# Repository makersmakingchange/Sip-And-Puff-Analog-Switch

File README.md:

# Sip and Puff Switch

The Sip and Puff Switch is an assistive technology that enables a user to control a device by using their mouth to "sip"(inhale) or "puff"(exhale) on a straw, tube or ‘wand’. It is primarily used by people with limited or no limb movement. The Sip and Puff Switch can be connected directly to an assistive device with a 3.5 mm jack or to a computer or smartphone using a suitable switch interface.

The Sip and Puff Switch has two 3.5 mm mono outputs so it can control two devices. The sip threshold and puff threshold are adjustable. The switch is powered by two CR2032 lithium coin cell batteries.

## More info at

- [Makers Making Change Project Page](https://www.makersmakingchange.com/project/sip-and-puff-switch/)

## Getting Started

### 1. Order the Off-The-Shelf Components
The [Bill of Materials](/Documentation/SPA_BOM_v1.0.xlsx) lists all of the parts and components required to build the Sip and Puff switch.

### 2. Order the Custom Printed Circuit Board (PCB)
The Sip and Puff Switch uses a custom PCB to mount all of the electronic components. Refer to [MMC_PCB_Fabrication_Manual](/Documentation/MMC_PCB_Fabrication_Manual.pdf) for information on how to order a custom PCB. For convenience, the final generated Gerber files for several PCB manufacturers are listed below. If you want to use a different manufacturer, instructions for converting the original [Eagle Files](/Design_Files/PCB/Eagle_Files) are also included in the MMC PCB Fabrication Manual.

| PCB Manufacturer                	| Website                                 	| Gerber Files                                                                                                        	|
|---------------------------------	|-----------------------------------------	|-------------------------------------------------------------------------------------------------------------	|
| JLCPCB                          	| https://jlcpcb.com/                     	|  [JLCPCB_Sip_And_Puff_Analog_Switch.zip](/Build_Files/PCB/JLCPCB_Sip_And_Puff_Analog_Switch.zip)             	|
| OSH Park                        	| https://oshpark.com/                    	| [OSHPark_Sip_And_Puff_Analog_Switch.zip](/Build_Files/PCB/OSHPark_Sip_And_Puff_Analog_Switch.zip)           	|
| Seeed Fusion PCB                	| https://www.seeedstudio.com/fusion.html 	| [Seeed_Fusion_Sip_And_Puff_Analog_Switch.zip](/Build_Files/PCB/Seeed_Fusion_Sip_And_Puff_Analog_Switch.zip) 	|

### 3. Print the 3D Printable components

Print the components for the enclosure and the mouthpiece mount: [3D Printing Files](/Build_Files/3D_Printing/). Total print time for the enclosure components is approximately 4.5 hours and for the mouthpiece mount components is approximately 2.5 hours.  

### 4. Assemble the Switch and Mouthpiece Mount

Reference the assembly instructions for the [Sip and Puff Switch](/Documentation/SPA_Assembly_v1.0.pdf) and the assembly instructions for the [Mouthpiece Stand](/Documentation/SPA_MPStand_Assembly_v1.0.pdf) for the tools and steps required to build each portion.

## Files

### Documentation
| Document                        	| Version 	| Link                                                                         	|
|---------------------------------	|---------	|------------------------------------------------------------------------------	|
| Design Specification            	| WIP     	|                                                                              	|
| Design Rationale                	| WIP     	|                                                                              	|
| Bill of Materials               	| 1.0     	| [SPA_BOM](/Documentation/SPA_BOM_v1.0.xlsx)                                  	|
| Assembly Guide                  	| 1.0     	| [SPA_Assembly](/Documentation/SPA_Assembly_v1.0.pdf)                         	|
| Mouthpiece Mount Assembly Guide 	| 1.0     	| [SPA_MPStand_Assembly](/Documentation/SPA_MPStand_Assembly_v1.0.pdf)         	|
| Maker Checklist                 	| 1.0     	| [SPA_Checklist](/Documentation/SPA_Checklist_v1.0.pdf)                       	|
| Quick Guide                     	| 1.0     	| [SPA_Checklist](/Documentation/SPA_Quick_Guide_v1.0.pdf)                      |
| User Guide                      	| 1.0     	| [SPA_Checklist](/Documentation/SPA_User_Guide_v1.0.pdf)                       |
| Changelog                       	| 1.0     	| [SPA_Changelog](/Documentation/SPA_Changelog_v1.0.pdf)                       	|
| PCB Fabrication Manual          	| 0.1     	| [MMC_PCB_Fabrication_Manual](/Documentation/MMC_PCB_Fabrication_Manual.pdf)  	|

### Design Files
 - [Enclosure CAD Files](/Design_Files/CAD/Enclosure)
 - [Mouthpiece Mount CAD Files](/Design_Files/CAD/Mouthpiece_Mount)
 - [PCB Files](/Design_Files/PCB/Eagle_Files)

### Build Files
 - [3D Printing Files](/Build_Files/3D_Printing)
 - [PCB Files](/Build_Files/PCB/Gerber_Files)

## License
Everything needed or used to design, make, test, or prepare the Analog Sip and Puff Switch is licensed under the CERN 2.0 Persmissive license <https://ohwr.org/project/cernohl/wikis/Documents/CERN-OHL-version-2> (CERN-OHL-P) .

Accompanying material such as instruction manuals, videos, and other copyrightable works that are useful but not necessary to design, make, test, or prepare the Analog Sip and Puff Switch are publshed under a Creative Commons Attribution-ShareAlike 4.0 license <https://creativecommons.org/licenses/by-sa/4.0/> (CC BY-SA 4.0)

<!-- ABOUT MMC START -->
## About Makers Making Change

Makers Making Change is a program of [Neil Squire](https://www.neilsquire.ca/), a Canadian non-profit that uses technology, knowledge, and passion to empower people with disabilities.

Makers Making Change leverages the capacity of community based Makers, Disability Professionals and Volunteers to develop and deliver affordable Open Source Assistive Technologies.

 - Website: [www.MakersMakingChange.com](https://www.makersmakingchange.com/)
 - GitHub: [makersmakingchange](https://github.com/makersmakingchange)
 - Bluesky: [@makersmakingchange.bsky.social](https://bsky.app/profile/makersmakingchange.bsky.social)
 - Instagram: [@makersmakingchange](https://www.instagram.com/makersmakingchange)
 - Facebook: [makersmakechange](https://www.facebook.com/makersmakechange)
 - LinkedIn: [Neil Squire Society](https://www.linkedin.com/company/neil-squire-society/)
 - Thingiverse: [makersmakingchange](https://www.thingiverse.com/makersmakingchange/about)
 - Printables: [MakersMakingChange](https://www.printables.com/@MakersMakingChange)

### Contact Us
For technical questions, to get involved, or to share your experience we encourage you to [visit our website](https://www.makersmakingchange.com/) or [contact us](https://www.makersmakingchange.com/s/contact).
<!-- ABOUT MMC END -->

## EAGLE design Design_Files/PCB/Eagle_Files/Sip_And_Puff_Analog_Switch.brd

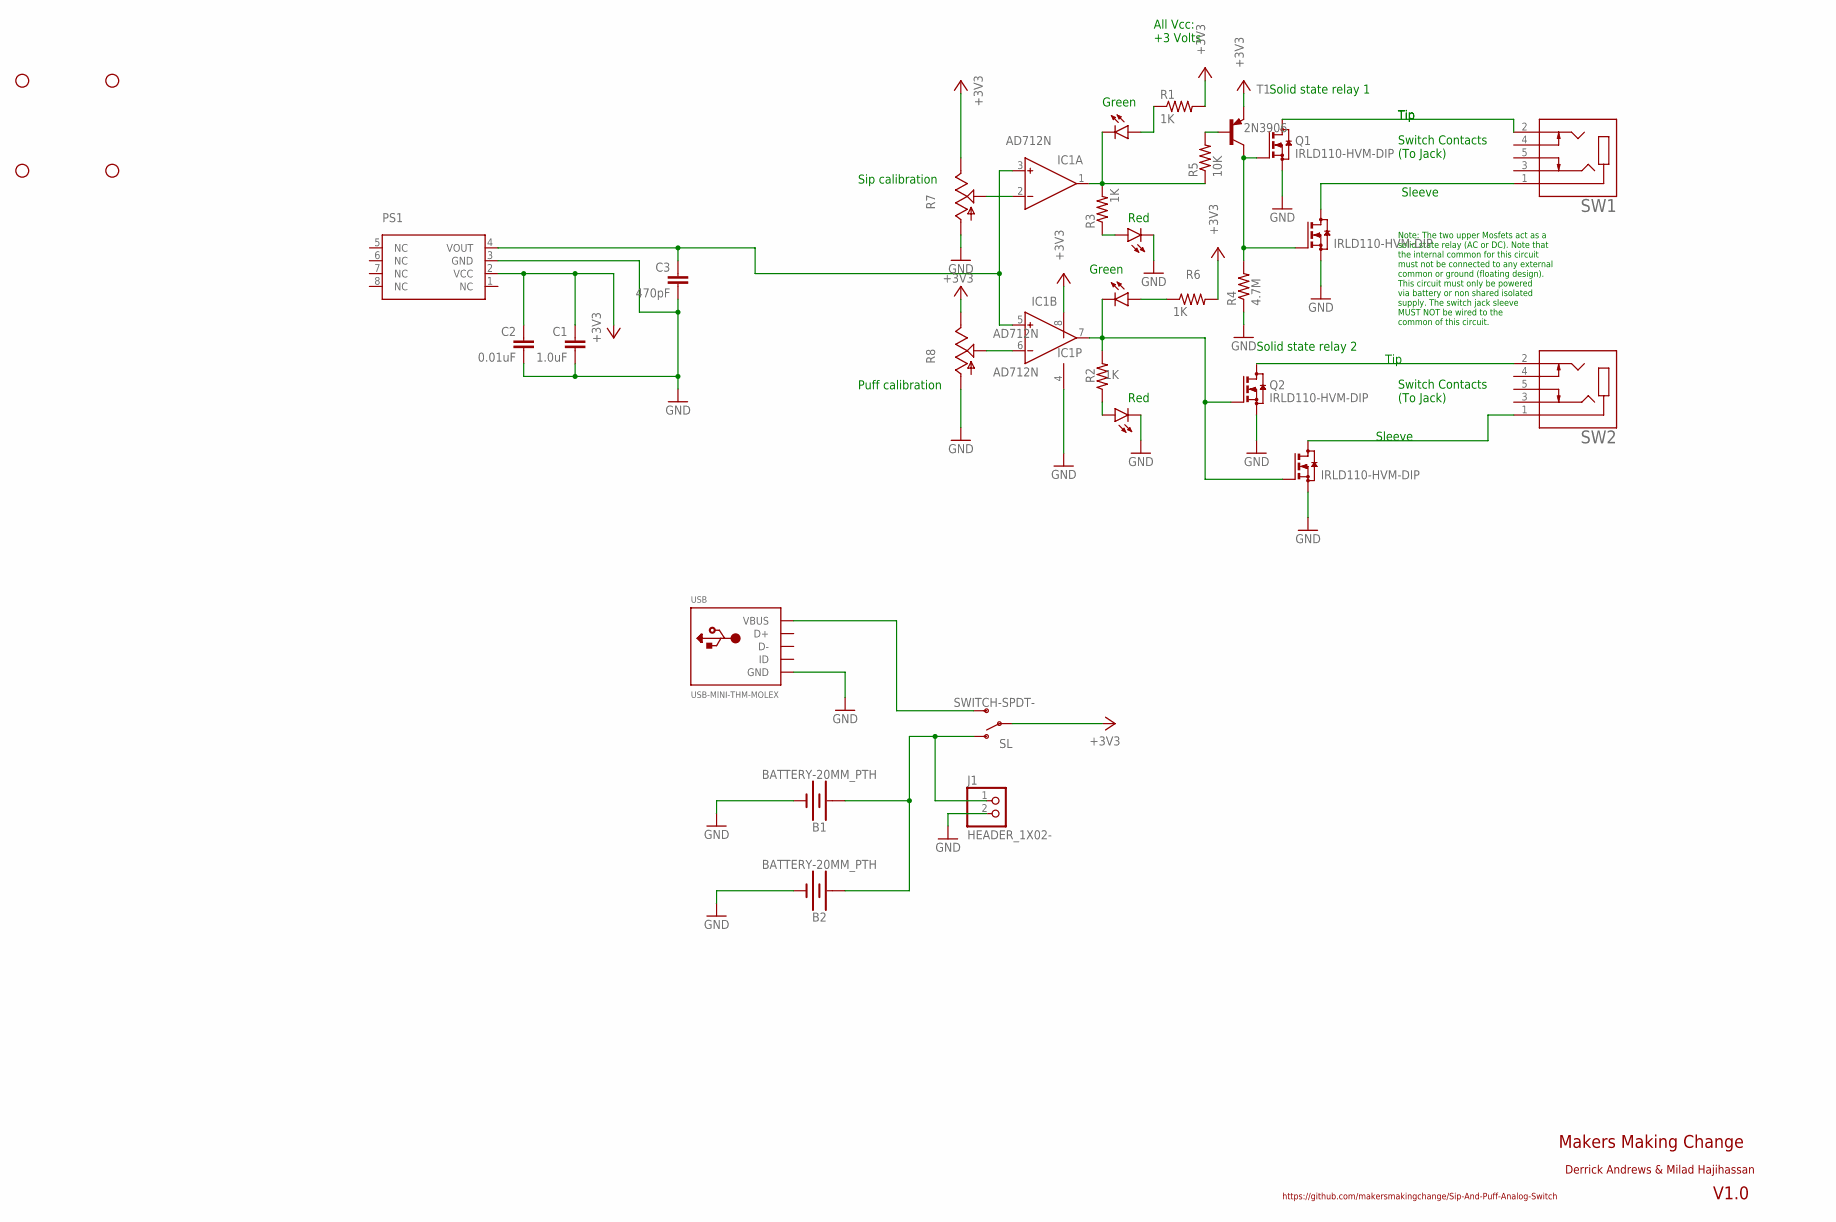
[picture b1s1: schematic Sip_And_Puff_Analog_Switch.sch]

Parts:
B1, B2: BATTERY-20MM_PTH; BATTCOM_20MM_PTH
C1: 1.0uF; CAP-PTH-SMALL-KIT
C2: 0.01uF; CAP-PTH-SMALL-KIT
C3: 470pF; CAP-PTH-SMALL-KIT
IC1: AD712N; DIL08
J1: HEADER_1X02-; 1X02
LED1, LED2: LED5MM-RED; LED_5MM_RED
LED3, LED4: LED5MM-GREEN; LED_5MM_GREEN
PS1: MPX-; MXP_SOP8
Q1, Q2, Q3, Q4: IRLD110-HVM-DIP; HVM-DIP
R1, R2, R3, R6: 1K; RESISTOR_0207/7
R4: 4.7M; RESISTOR_0207/7
R5: 10K; RESISTOR_0207/7
R7, R8: TRIM-3386C; 3386C
SL: SWITCH-SPDT-; SPDT-RA
STANDOFF1, STANDOFF2, STANDOFF3, STANDOFF4: STAND-OFF-; STAND-OFF
SW1, SW2: CUI_SJ1-3535NGSJ1-3535NG; CUI_SJ1-3535NG
T1: 2N3906; TO92-EBC
USB: USB-MINI-THM-MOLEX; USB-MINIB-THM-MOLEX

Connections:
+3V3: C1.1, C2.1, IC1.8 (V+), PS1.2 (VCC), R1.2, R6.2, R7.E, R8.E, SL.2, T1.E
GND: B1.-, B2.-, C1.2, C2.2, C3.2, IC1.4 (V-), J1.2, LED1.K (C), LED2.K (C), PS1.3 (GND), Q1.2 (S), Q2.2 (S), Q3.2 (S), Q4.2 (S), R4.1, R7.A, R8.A, USB.GND
unnamed: IC1.7 (OUT), LED4.K (C), Q2.1 (G), Q4.1 (G), R2.2
unnamed: SL.3 (S), USB.VBUS
unnamed: LED4.A, R6.1
unnamed: B1.+, B2.+, J1.1, SL.1 (O)
unnamed: Q3.3 (D), SW1.1
unnamed: Q1.3 (D), SW1.2
unnamed: Q1.1 (G), Q3.1 (G), R4.2, T1.C
unnamed: R5.2, T1.B
unnamed: IC1.1 (OUT), LED3.K (C), R3.2, R5.1
unnamed: IC1.2 (IN-), R7.S
unnamed: IC1.6 (IN-), R8.S
unnamed: C3.1, IC1.3 (IN+), IC1.5 (IN+), PS1.4 (VOUT)
unnamed: Q2.3 (D), SW2.2
unnamed: Q4.3 (D), SW2.1
unnamed: LED3.A, R1.1
unnamed: LED2.A, R2.1
unnamed: LED1.A, R3.1

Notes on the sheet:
Makers Making Change
V1.0
https://github.com/makersmakingchange/Sip-And-Puff-Analog-Switch
Derrick Andrews & Milad Hajihassan
All Vcc: +3 Volts
Switch Contacts (To Jack)
Note: The two upper Mosfets act as a solid state relay (AC or DC). Note that the internal common for this circuit must not be connected to any external common or ground (floating design). This circuit must only be powered via battery or non shared isolated supply. The switch jack sleeve MUST NOT be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
Tip
Sleeve
Solid state relay 1
Solid state relay 2
Sip calibration
Puff calibration
Green
Red

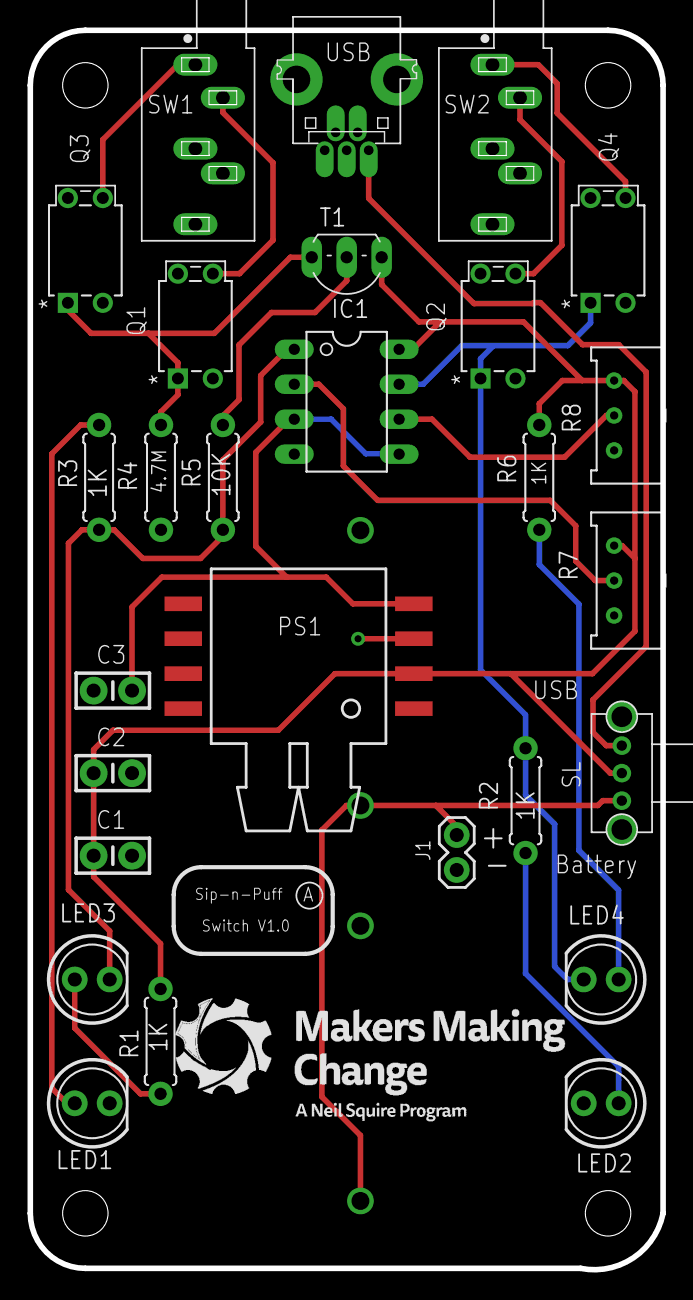
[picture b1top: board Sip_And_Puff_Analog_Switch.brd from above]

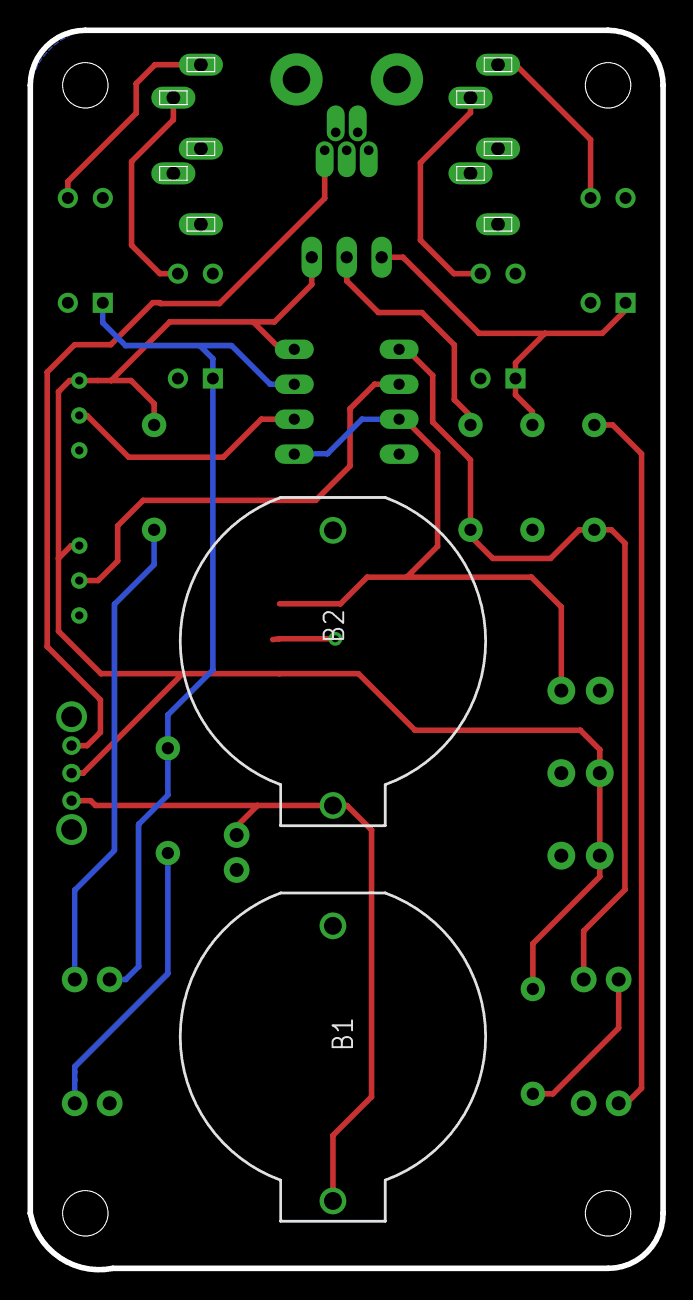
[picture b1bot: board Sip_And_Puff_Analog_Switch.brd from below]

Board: 2 copper layers, 46.0 x 90.1 mm, 33 parts (2 on the bottom side), 19 nets.

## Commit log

2020-07-02 Pre-publish commit
2020-07-02 Update and reorganize
2020-07-02 Rename instructions to assembly for clarity
2020-07-03 Add Quick Guide and User Guide
2020-07-03 Quick Guide and User Guide
2020-07-06 Update BOM
2020-07-07 Update SPA_BOM_v1.0.xlsx
    Correct M3 screw length
2020-07-08 Convert to stl binary
    Binary version of stl rather than text version provides a download link and reduces confusion.
2020-07-10 Update SPA_BOM_v1.0.xlsx
    Add missing two position header.
2020-07-10 Update README.md
    Update Forum Link and fix links
2020-08-31 Added base for 4-lobed T-nut option
    The BOM suggests a 4-lobed T-nut, but the STL files only had a base for the rarer triple-lobed T-nut. This additional file fixes that.
    Generated from the existing *SPA_MP_Base.stl* file using OpenSCAD and this very small (but slow) script:
    // mmc sip and puff base fixed for 4-lobe t-nuts - scruss, 2020-08
    bbox = [ 35.000000, 35.000000, 9.000000 ];
    minima = [ 107.500000, 87.500000, 0.000000 ];
    module b() {
2020-10-13 Update SPA_MP_Lower_Swivel.stl
    Replace text-based stl wth binary version for consistency.
2020-10-13 Add 3mf files
2022-04-25 Update LICENSE.md
    Correct naming.
2022-04-25 Update README.md
    Correct license.
2025-04-10 Add Update About MMC GitHub Action
2025-04-12 Update About MMC Section

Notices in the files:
parts and their libraries:
SparkFun-Aesthetics: Licensing: Creative Commons ShareAlike 4.0 International - https://creativecommons.org/licenses/by-sa/4.0
